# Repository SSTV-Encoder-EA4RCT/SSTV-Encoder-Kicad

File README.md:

# PCB de SSTV Encoder

Se ha utiliza la versión 5.1.5 de Kicad para el desarrollo del proyecto. Para instalarlo bastaría con importar `sstv-enconder/sstv-encoder.pro` a Kicad.

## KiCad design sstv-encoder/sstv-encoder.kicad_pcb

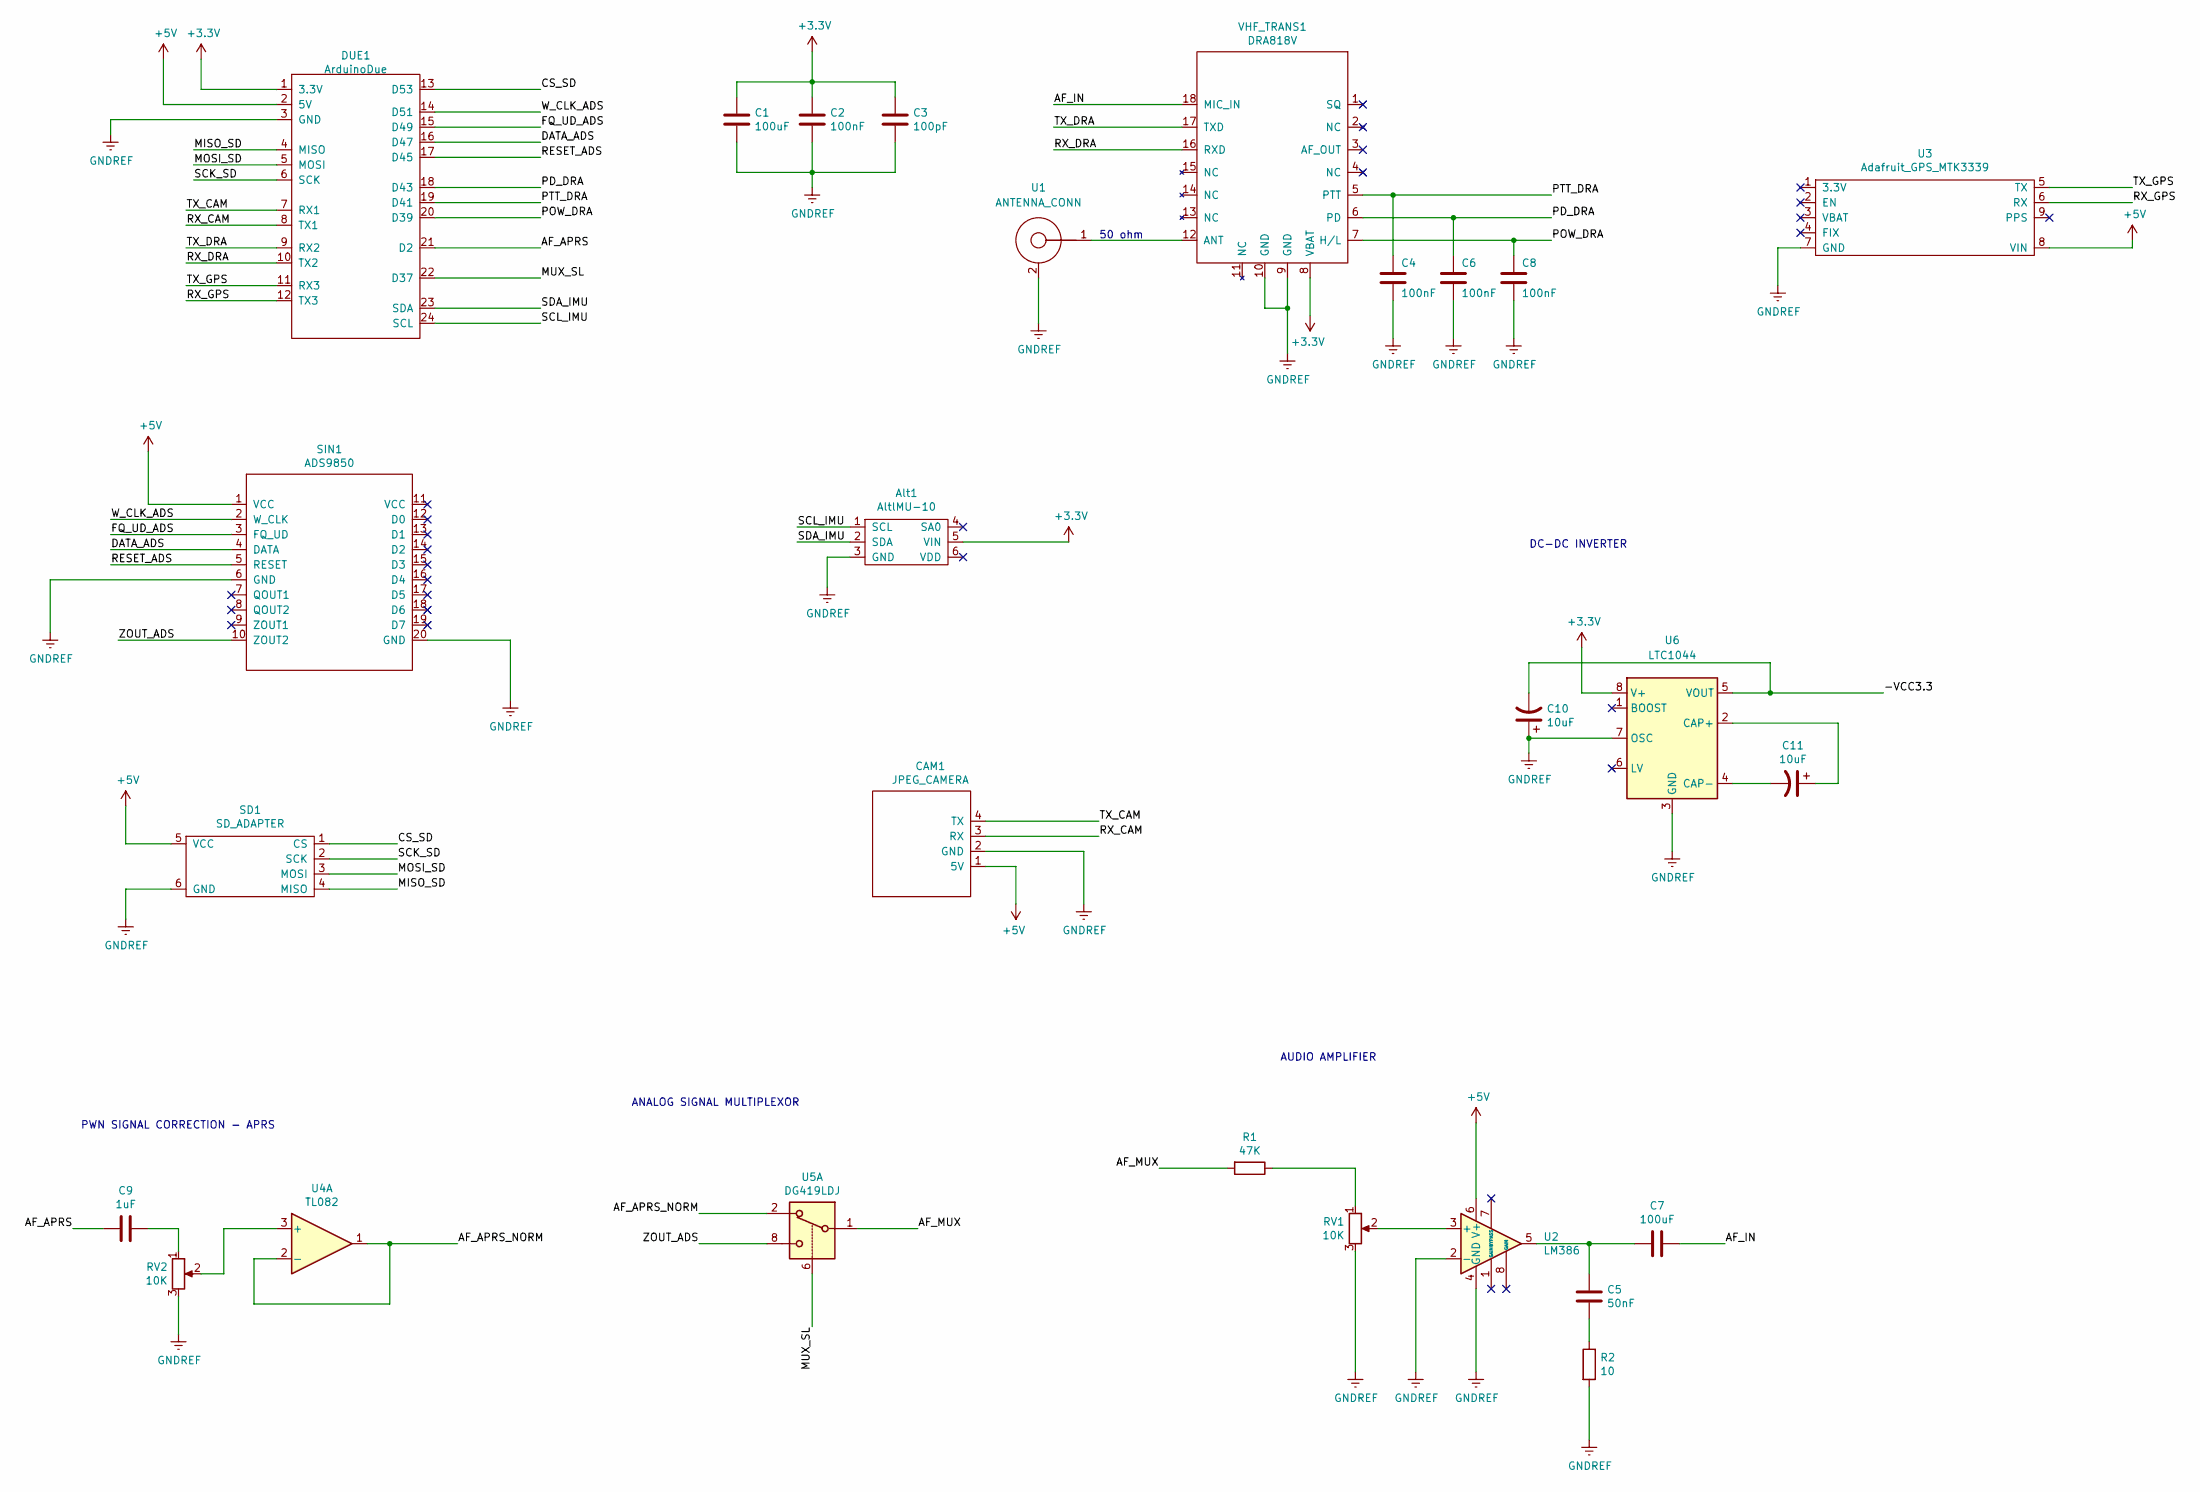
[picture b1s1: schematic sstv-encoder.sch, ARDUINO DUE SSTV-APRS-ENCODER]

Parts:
Alt1: AltlMU-10; AltIMU-10
C1, C7: 100uF; CP_Radial_D5.0mm_P2.50mm
C2, C4, C6, C8: 100nF; C_Rect_L4.0mm_W2.5mm_P2.50mm
C3: 100pF; C_Rect_L4.0mm_W2.5mm_P2.50mm
C5: 50nF; C_Rect_L7.0mm_W2.0mm_P5.00mm
C9: 1uF; CP_Radial_D5.0mm_P2.50mm
C10, C11: 10uF; CP_Radial_D5.0mm_P2.50mm
CAM1: JPEG_CAMERA; vc0706
DUE1: ArduinoDue; Due
R1: 47K; R_Axial_DIN0204_L3.6mm_D1.6mm_P5.08mm_Horizontal
R2: 10; R_Axial_DIN0204_L3.6mm_D1.6mm_P5.08mm_Horizontal
RV1, RV2: 10K; Potentiometer_Piher_PT-10-V10_Vertical
SD1: SD_ADAPTER; MicroSD_Adapter
SIN1: ADS9850; AD9850
U1: ANTENNA_CONN; SMA_conn
U2: LM386; DIP-8_W7.62mm
U3: Adafruit_GPS_MTK3339; Adafruit_GPS
U4: TL082; DIP-8_W7.62mm
U5: DG419LDJ; DIP-8_W7.62mm
U6: LTC1044; DIP-8_W7.62mm
VHF_TRANS1: DRA818V

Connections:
+3V3: Alt1.5 (VIN), C1.1, C2.1, C3.1, DUE1.1 (3.3V), U6.8 (V+), VHF_TRANS1.8 (VBAT)
+5V: CAM1.1 (5V), DUE1.2 (5V), SD1.5 (VCC), SIN1.1 (VCC), U2.6 (V+), U3.8 (VIN)
/-VCC3.3: C10.2, U6.5 (VOUT)
/AF_APRS: C9.2, DUE1.21 (D2)
/AF_APRS_NORM: U4.1, U4.2 (-), U5.2
/AF_IN: C7.1, VHF_TRANS1.18 (MIC_IN)
/AF_MUX: R1.2, U5.1
/CS_SD: DUE1.13 (D53), SD1.1 (CS)
/DATA_ADS: DUE1.16 (D47), SIN1.4 (DATA)
/FQ_UD_ADS: DUE1.15 (D49), SIN1.3 (FQ_UD)
/MISO_SD: DUE1.4 (MISO), SD1.4 (MISO)
/MOSI_SD: DUE1.5 (MOSI), SD1.3 (MOSI)
/MUX_SL: DUE1.22 (D37), U5.6
/PD_DRA: C6.1, DUE1.18 (D43), VHF_TRANS1.6 (PD)
/POW_DRA: C8.1, DUE1.20 (D39), VHF_TRANS1.7 (H/L)
/PTT_DRA: C4.1, DUE1.19 (D41), VHF_TRANS1.5 (PTT)
/RESET_ADS: DUE1.17 (D45), SIN1.5 (RESET)
/RX_CAM: CAM1.3 (RX), DUE1.8 (TX1)
/RX_DRA: DUE1.10 (TX2), VHF_TRANS1.16 (RXD)
/RX_GPS: DUE1.12 (TX3), U3.6 (RX)
/SCK_SD: DUE1.6 (SCK), SD1.2 (SCK)
/SCL_IMU: Alt1.1 (SCL), DUE1.24 (SCL)
/SDA_IMU: Alt1.2 (SDA), DUE1.23 (SDA)
/TX_CAM: CAM1.4 (TX), DUE1.7 (RX1)
/TX_DRA: DUE1.9 (RX2), VHF_TRANS1.17 (TXD)
/TX_GPS: DUE1.11 (RX3), U3.5 (TX)
/W_CLK_ADS: DUE1.14 (D51), SIN1.2 (W_CLK)
/ZOUT_ADS: SIN1.10 (ZOUT2), U5.8
GNDREF: Alt1.3 (GND), C1.2, C2.2, C3.2, C4.2, C6.2, C8.2, C10.1, CAM1.2 (GND), DUE1.3 (GND), R2.2, RV1.3, RV2.3, SD1.6 (GND), SIN1.6 (GND), SIN1.20 (GND), U1.2, U2.2 (-), U2.4 (GND), U3.7 (GND), U6.3 (GND), U6.7 (OSC), VHF_TRANS1.9 (GND), VHF_TRANS1.10 (GND)
unnamed: C5.1, C7.2, U2.5
unnamed: C5.2, R2.1
unnamed: C9.1, RV2.1
unnamed: C11.1, U6.2 (CAP+)
unnamed: C11.2, U6.4 (CAP-)
unnamed: R1.1, RV1.1
unnamed: RV1.2, U2.3 (+)
unnamed: RV2.2, U4.3 (+)
unnamed: U1.1, VHF_TRANS1.12 (ANT)

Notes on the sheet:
50 ohm
PWN SIGNAL CORRECTION - APRS
ANALOG SIGNAL MULTIPLEXOR
AUDIO AMPLIFIER
DC-DC INVERTER

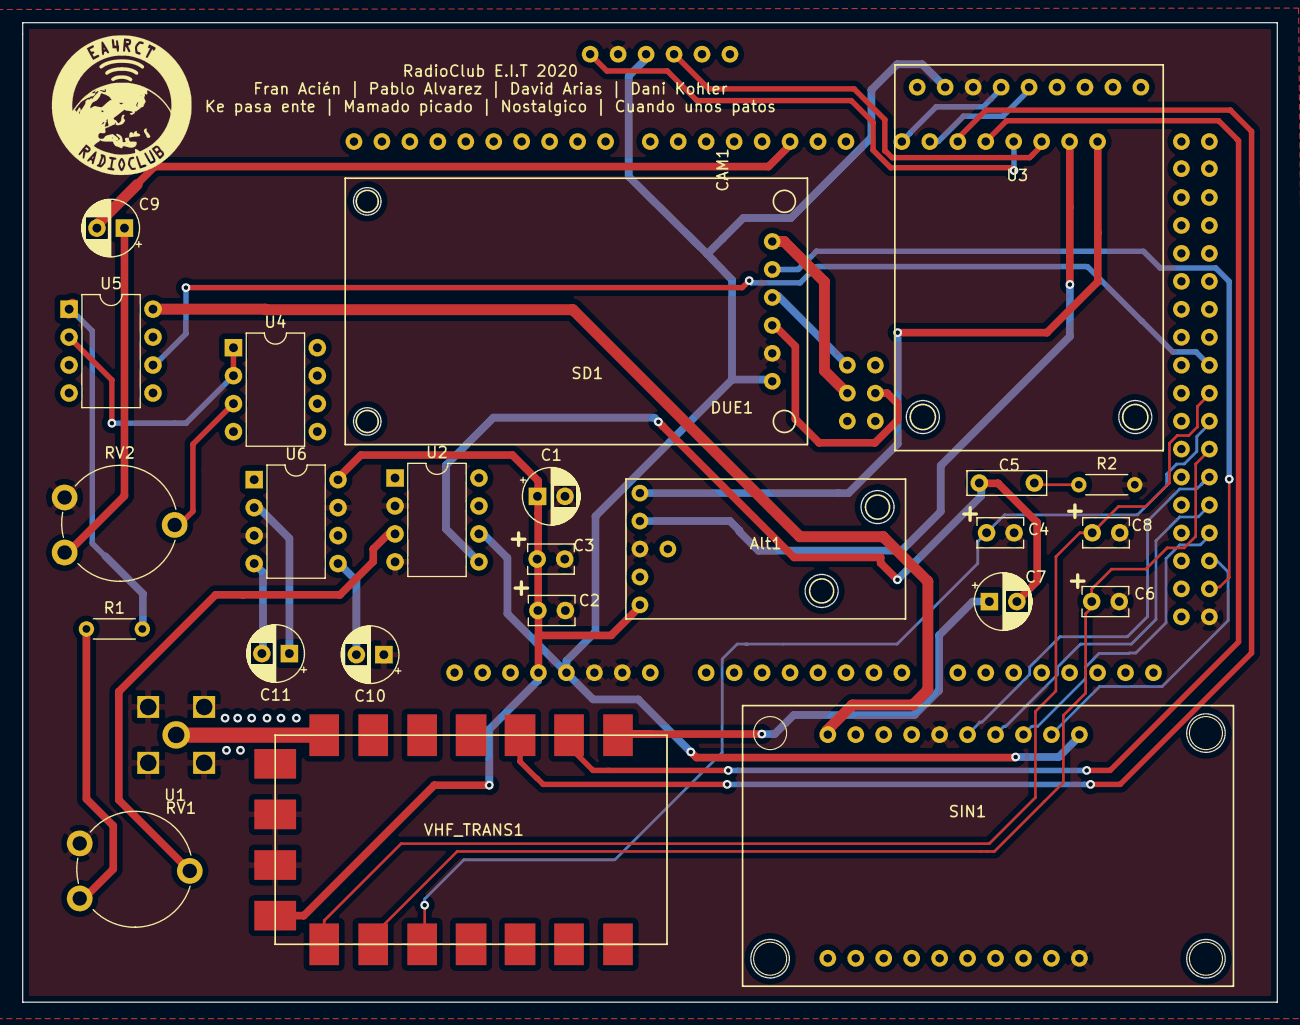
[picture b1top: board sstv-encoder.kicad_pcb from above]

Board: 2 copper layers, 114.0 x 89.0 mm, 27 parts (0 on the bottom side), 38 nets.

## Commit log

2019-07-30 adding components library
2020-03-14 añadiendo cosillas
2020-03-17 updating component footprint
2020-03-19 adding new things
2020-03-30 actualziando cosillas
2020-03-30 add simple readme
2020-04-06 update sch
2020-04-06 update lib
2020-05-12 update schematic
2020-05-15 update pdf
2020-12-01 finish pcb
2020-12-01 fix error
2020-12-01 fix footprint error
